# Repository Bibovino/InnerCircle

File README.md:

# InnerCircle
Coffee Request Interface for shared coworking space, cube farms or general offices.

The InnerCircle can consist of multiple nodes and a base, which are connected over WiFi. The base acts as a Hotspot, enabling the nodes in range to connect, send and receive requests. Each node can display the status of up to 12 selected nodes in the same network. The nodes are selected in a webinterface and allow the configuration of each node. A user can send requests for coffee-breaks or spontaneuos meetings by selecting a led on the circular PCB. The request is displayed on the corresponding node, if the involved user has the requesting user in his inner circle.

The node consists of a PCB, a small microcontroller and a GPIO-Multiplexer. On the board are multiple RGB-Leds, which are Daidychained into a circle. The input for each LED is registered by a voltage drop over selected traces on the pcb.

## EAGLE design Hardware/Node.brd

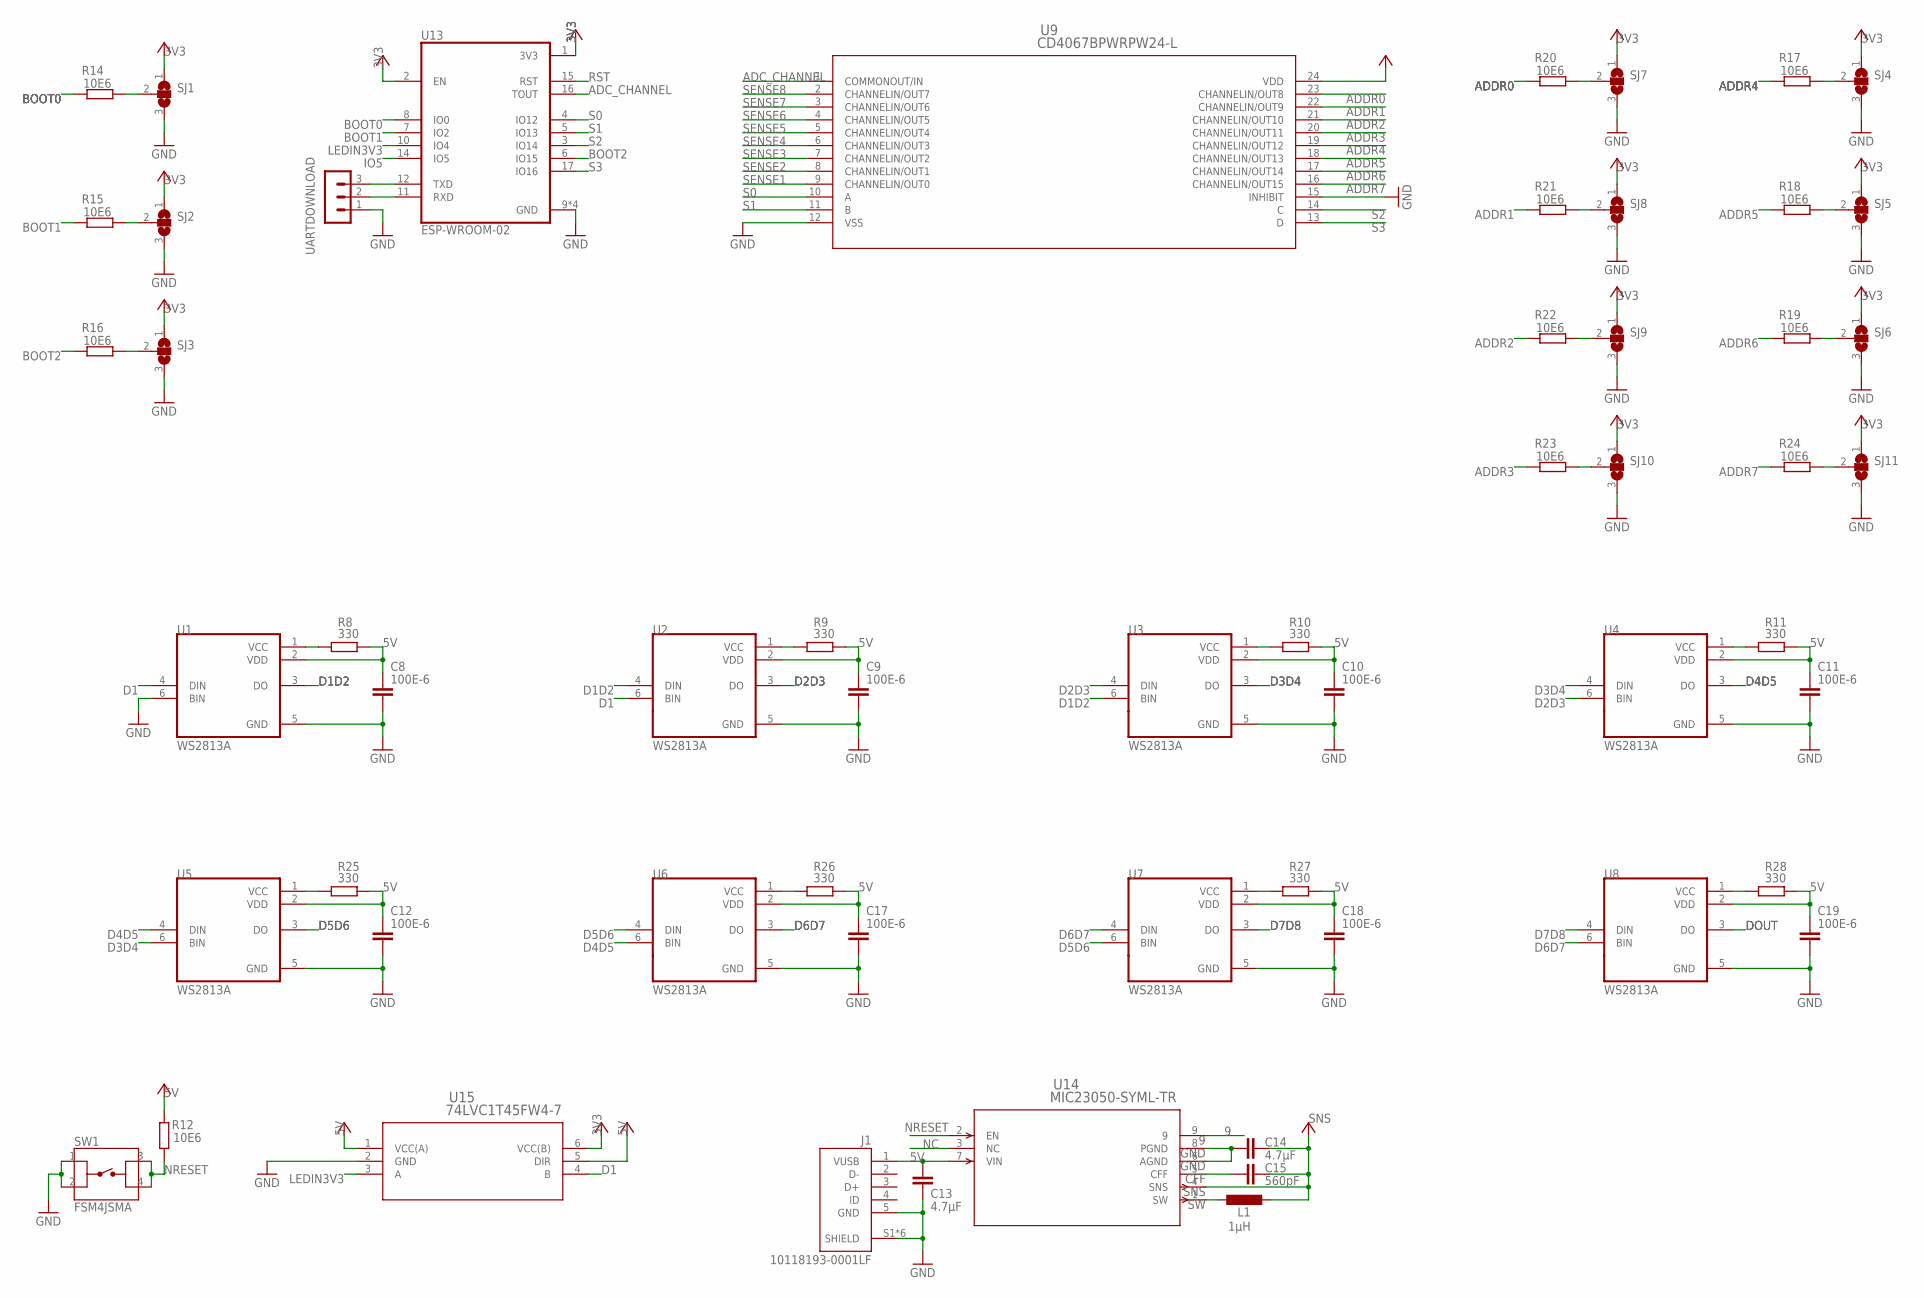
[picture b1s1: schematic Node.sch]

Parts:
C8, C9, C10, C11, C12, C17, C18, C19: 100E-6; C0402K
C13, C14: 4.7µF; C0603
C15: 560pF; C0603
J1: 10118193-0001LF; FCI_10118193-0001LF
L1: 1µH; L1812
R8, R9, R10, R11, R25, R26, R27, R28: 330; R0402
R12, R14, R15, R16, R17, R18, R19, R20, R21, R22, R23, R24: 10E6; R0402
SJ1, SJ2, SJ3, SJ4, SJ5, SJ6, SJ7, SJ8, SJ9, SJ10, SJ11: SJ2W; SJ_2
SW1: FSM4JSMA; TE_FSM4JSMA
U1, U2, U3, U4, U5, U6, U7, U8: WS2813A; LED_WS2813A
U9: CD4067BPWRPW24-L; PW24-L
U13: ESP-WROOM-02; MODULE_ESP-WROOM-02
U14: MIC23050-SYML-TR; MLF-8_ML
U15: 74LVC1T45FW4-7; X2-DFN1010-6
UARTDOWNLOAD: MA03-1

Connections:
3V3: SJ1.1, SJ2.1, SJ3.1, SJ4.1, SJ5.1, SJ6.1, SJ7.1, SJ8.1, SJ9.1, SJ10.1, SJ11.1, U13.1 (3V3), U15.6 (VCC(B))
5V: C8.1, C13.1, J1.1 (VUSB), R8.1, R12.2, U1.2 (VDD), U14.7 (VIN), U15.1 (VCC(A)), U15.5 (DIR)
9: U14.9
ADC_CHANNEL: U9.1 (COMMONOUT/IN), U13.16 (TOUT)
ADDR0: R20.2, U9.23 (CHANNELIN/OUT8)
ADDR1: R21.2, U9.22 (CHANNELIN/OUT9)
ADDR2: R22.2, U9.21 (CHANNELIN/OUT10)
ADDR3: R23.2, U9.20 (CHANNELIN/OUT11)
ADDR4: R17.2, U9.19 (CHANNELIN/OUT12)
ADDR5: R18.2, U9.18 (CHANNELIN/OUT13)
ADDR6: R19.2, U9.17 (CHANNELIN/OUT14)
ADDR7: R24.2, U9.16 (CHANNELIN/OUT15)
BOOT0: R14.2, U13.8 (IO0)
BOOT1: R15.2, U13.7 (IO2)
BOOT2: R16.2, U13.6 (IO15)
CFF: C15.1, U14.5 (CFF)
D1: U1.4 (DIN), U2.6 (BIN), U15.4 (B)
D1D2: U1.3 (DO), U2.4 (DIN)
D2D3: U2.3 (DO), U3.4 (DIN)
D3D4: U3.3 (DO), U4.4 (DIN)
D4D5: U4.3 (DO), U5.4 (DIN)
D5D6: U5.3 (DO), U6.4 (DIN)
D6D7: U6.3 (DO), U7.4 (DIN)
D7D8: U7.3 (DO), U8.4 (DIN)
DOUT: U8.3 (DO)
GND: C8.2, C9.2, C10.2, C11.2, C12.2, C13.2, C14.1, C17.2, C18.2, C19.2, J1.5 (GND), J1.S1 (SHIELD), J1.S2 (SHIELD), J1.S3 (SHIELD), J1.S4 (SHIELD), J1.S5 (SHIELD), J1.S6 (SHIELD), SJ1.3, SJ2.3, SJ3.3, SJ4.3, SJ5.3, SJ6.3, SJ7.3, SJ8.3, SJ9.3, SJ10.3, SJ11.3, SW1.1, SW1.2, U1.5 (GND), U1.6 (BIN), U2.5 (GND), U3.5 (GND), U4.5 (GND), U5.5 (GND), U6.5 (GND), U7.5 (GND), U8.5 (GND), U9.12 (VSS), U9.15 (INHIBIT), U13.9 (GND), U13.13 (GND), U13.18 (GND), U13.19 (GND), U14.6 (AGND), U14.8 (PGND), U15.2 (GND), UARTDOWNLOAD.1
IO5: U13.14 (IO5)
LEDIN3V3: U13.10 (IO4), U15.3 (A)
unnamed: R14.1, SJ1.2
unnamed: R8.2, U1.1 (VCC)
unnamed: R9.2, U2.1 (VCC)
unnamed: C9.1, R9.1, U2.2 (VDD)
unnamed: R10.2, U3.1 (VCC)
unnamed: C10.1, R10.1, U3.2 (VDD)
unnamed: R11.2, U4.1 (VCC)
unnamed: C11.1, R11.1, U4.2 (VDD)
unnamed: R25.2, U5.1 (VCC)
unnamed: C12.1, R25.1, U5.2 (VDD)
unnamed: R26.2, U6.1 (VCC)
unnamed: C17.1, R26.1, U6.2 (VDD)
unnamed: R15.1, SJ2.2
unnamed: R16.1, SJ3.2
unnamed: R17.1, SJ4.2
unnamed: R18.1, SJ5.2
unnamed: R19.1, SJ6.2
unnamed: R20.1, SJ7.2
unnamed: R21.1, SJ8.2
unnamed: R22.1, SJ9.2
unnamed: R23.1, SJ10.2
unnamed: R27.2, U7.1 (VCC)
unnamed: C18.1, R27.1, U7.2 (VDD)
unnamed: R28.2, U8.1 (VCC)
unnamed: C19.1, R28.1, U8.2 (VDD)
unnamed: R24.1, SJ11.2
NC: U14.3 (NC)
NRESET: R12.1, SW1.3, SW1.4, U14.2 (EN)
RST: U13.15 (RST)
RX: U13.11 (RXD), UARTDOWNLOAD.2
S0: U9.10 (A), U13.4 (IO12)
S1: U9.11 (B), U13.5 (IO13)
S2: U9.14 (C), U13.3 (IO14)
S3: U9.13 (D), U13.17 (IO16)
SENSE1: U9.9 (CHANNELIN/OUT0)
SENSE2: U9.8 (CHANNELIN/OUT1)
SENSE3: U9.7 (CHANNELIN/OUT2)
SENSE4: U9.6 (CHANNELIN/OUT3)
SENSE5: U9.5 (CHANNELIN/OUT4)
SENSE6: U9.4 (CHANNELIN/OUT5)
SENSE7: U9.3 (CHANNELIN/OUT6)
SENSE8: U9.2 (CHANNELIN/OUT7)
SNS: C14.2, C15.2, L1.2, U14.4 (SNS)
SW: L1.1, U14.1 (SW)
TX: U13.12 (TXD), UARTDOWNLOAD.3
VCC: U9.24 (VDD), U13.2 (EN)

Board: 2 copper layers, 58 parts (58 on the bottom side), 61 nets, no tracks yet.

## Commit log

2019-10-31 Update README.md
    Initial Commit with small changes to README.md
    Seperate document needs to be created.
2019-10-31 Datasheet for LEDs
2019-11-02 V0.1 Start with layout and possible ic´s
2019-11-03 Modified Hardware and added eagle libs.
2019-12-07 Modified Node
2020-01-16 Adapted Circuit
